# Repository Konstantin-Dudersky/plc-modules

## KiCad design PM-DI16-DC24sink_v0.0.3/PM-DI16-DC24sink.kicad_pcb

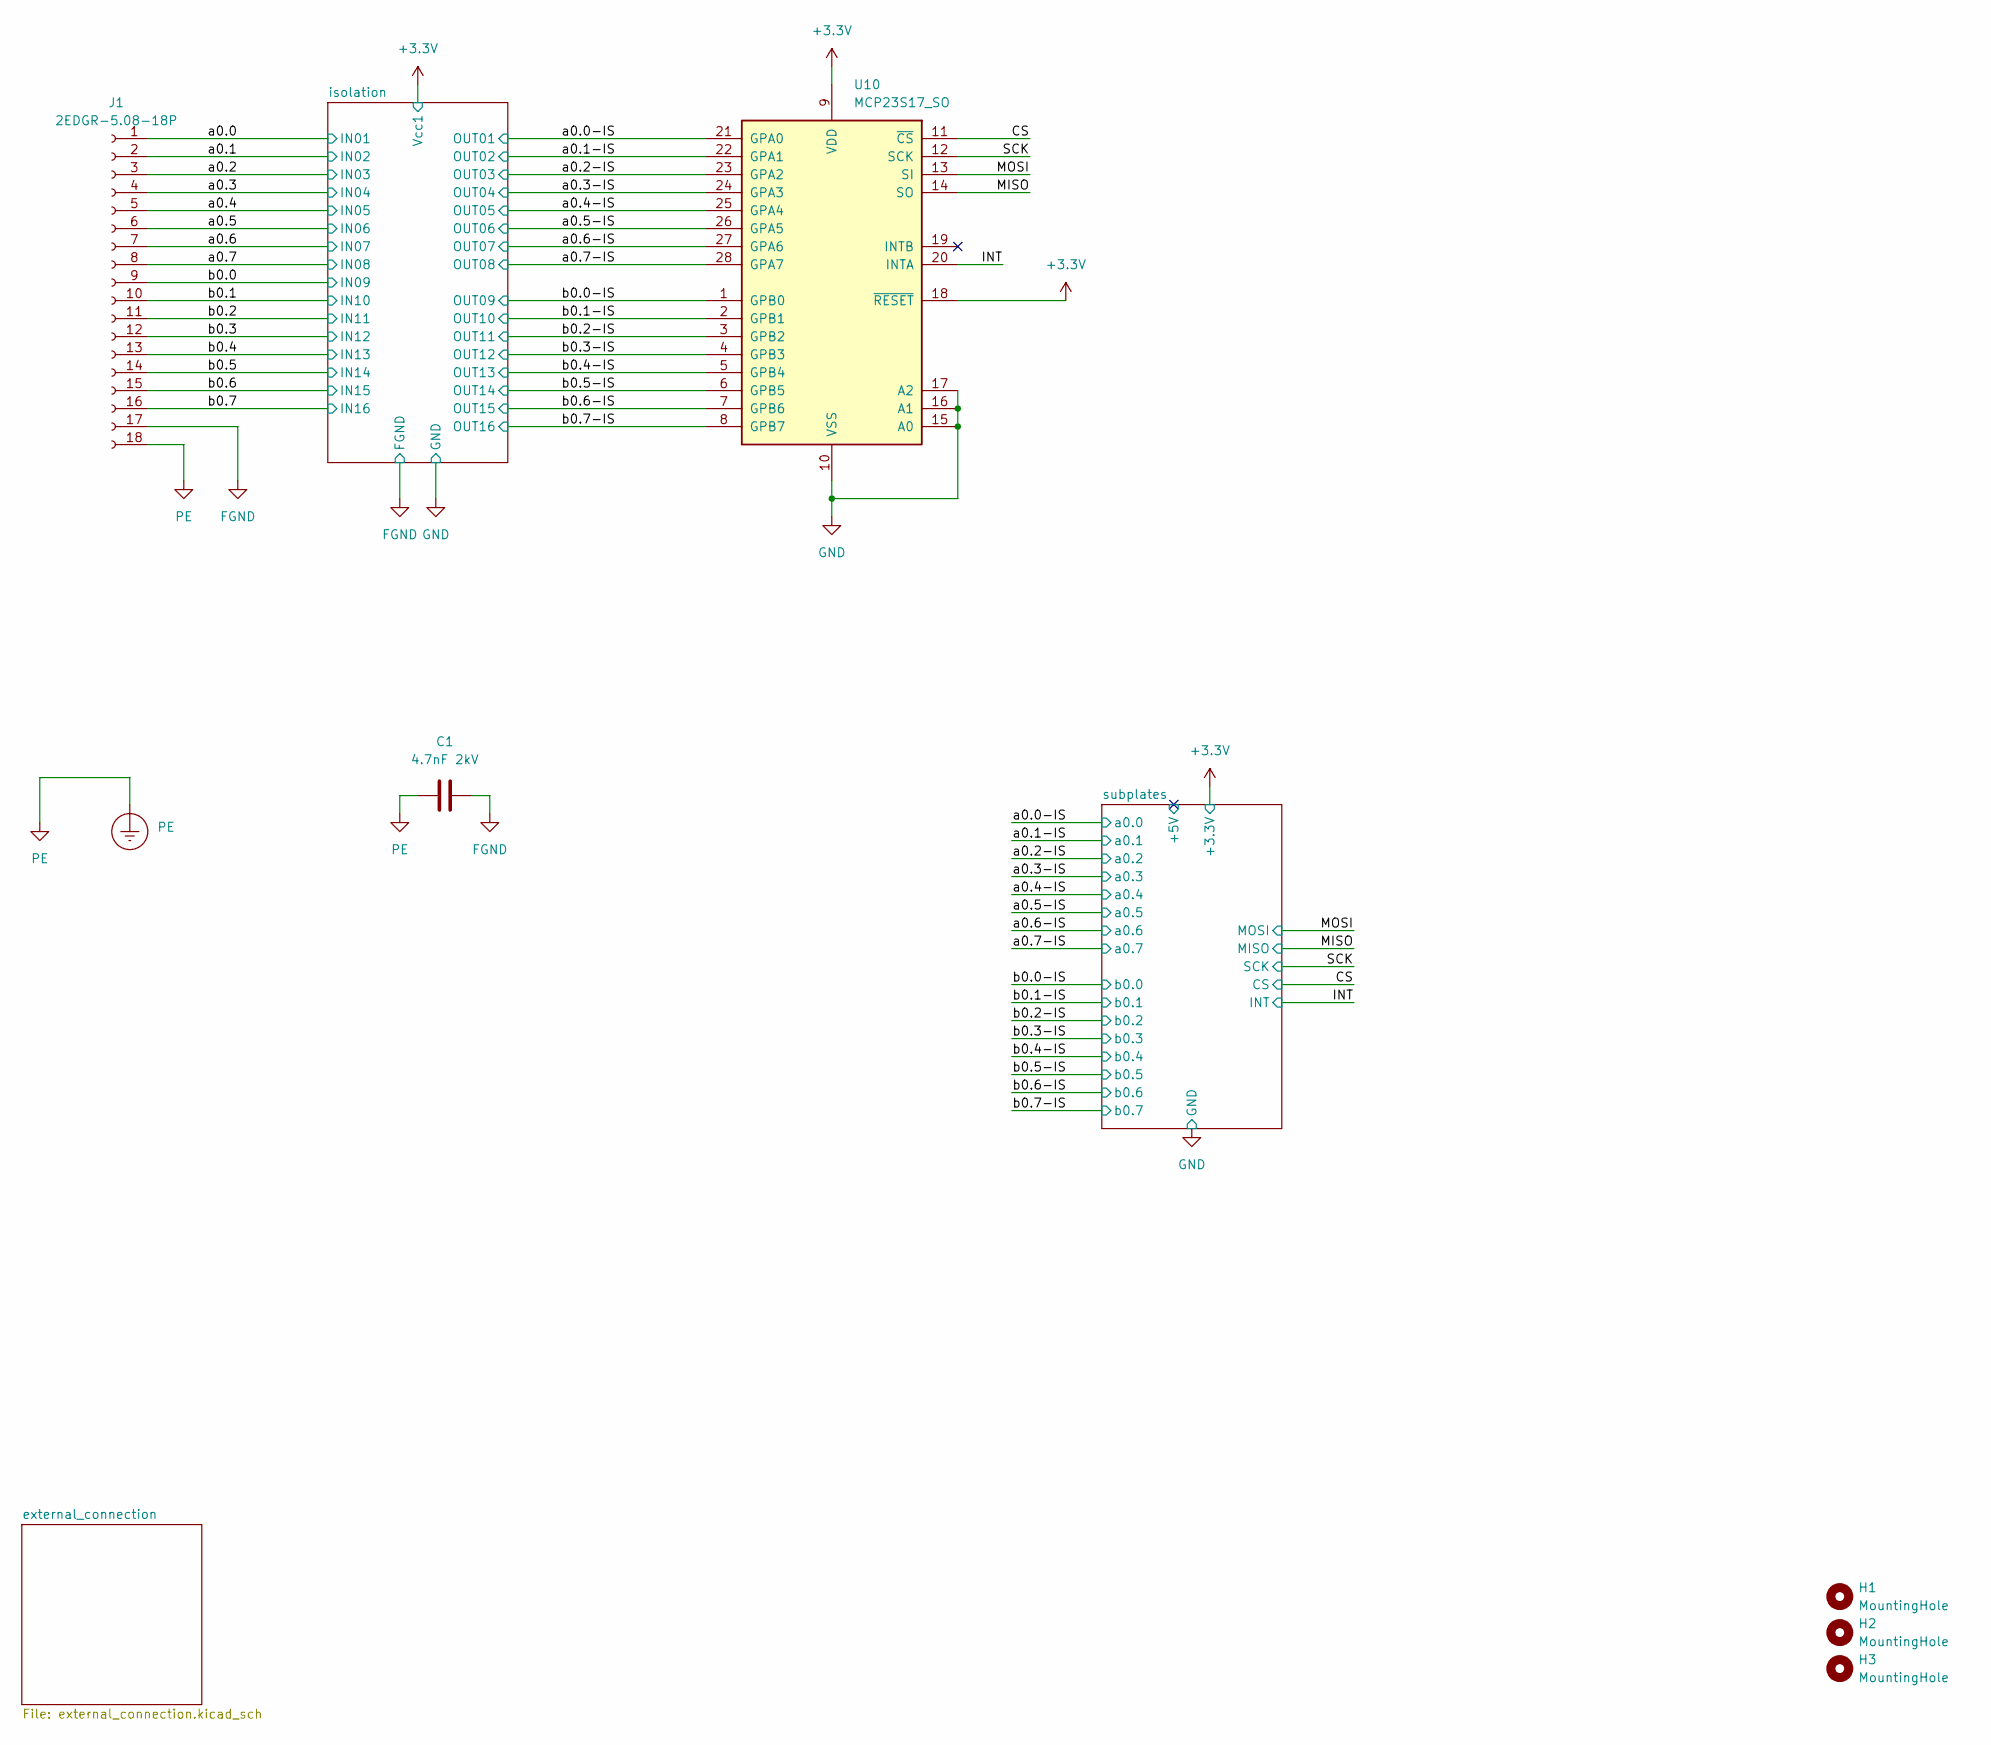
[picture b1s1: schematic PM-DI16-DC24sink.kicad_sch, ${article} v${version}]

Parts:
C1: 4.7nF 2kV; C_1812_4532Metric_Pad1.57x3.40mm_HandSolder; part_ipn C_4.7nF_2kV_1812
H1, H2, H3: MountingHole; MountingHole_3.2mm_M3
J1: 2EDGR-5.08-18P; Degson_2EDGR-5.08-18P; part_ipn 2EDGR-5.08-18P
PE1: PE
U10: MCP23S17_SO; SOIC-28W_7.5x17.9mm_P1.27mm; part_ipn MCP23S17-E/SO

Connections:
+3.3V: U10.9 (VDD), U10.18 (~RESET); also elsewhere on the board
/CS: U10.11 (~CS); also elsewhere on the board
/MISO: U10.14 (SO); also elsewhere on the board
/MOSI: U10.13 (SI); also elsewhere on the board
/SCK: U10.12 (SCK); also elsewhere on the board
/a0.0: J1.1; also elsewhere on the board
/a0.0-IS: U10.21 (GPA0); also elsewhere on the board
/a0.1: J1.2; also elsewhere on the board
/a0.1-IS: U10.22 (GPA1); also elsewhere on the board
/a0.2: J1.3; also elsewhere on the board
/a0.2-IS: U10.23 (GPA2); also elsewhere on the board
/a0.3: J1.4; also elsewhere on the board
/a0.3-IS: U10.24 (GPA3); also elsewhere on the board
/a0.4: J1.5; also elsewhere on the board
/a0.4-IS: U10.25 (GPA4); also elsewhere on the board
/a0.5: J1.6; also elsewhere on the board
/a0.5-IS: U10.26 (GPA5); also elsewhere on the board
/a0.6: J1.7; also elsewhere on the board
/a0.6-IS: U10.27 (GPA6); also elsewhere on the board
/a0.7: J1.8; also elsewhere on the board
/a0.7-IS: U10.28 (GPA7); also elsewhere on the board
/b0.0: J1.9; also elsewhere on the board
/b0.0-IS: U10.1 (GPB0); also elsewhere on the board
/b0.1: J1.10; also elsewhere on the board
/b0.1-IS: U10.2 (GPB1); also elsewhere on the board
/b0.2: J1.11; also elsewhere on the board
/b0.2-IS: U10.3 (GPB2); also elsewhere on the board
/b0.3: J1.12; also elsewhere on the board
/b0.3-IS: U10.4 (GPB3); also elsewhere on the board
/b0.4: J1.13; also elsewhere on the board
/b0.4-IS: U10.5 (GPB4); also elsewhere on the board
/b0.5: J1.14; also elsewhere on the board
/b0.5-IS: U10.6 (GPB5); also elsewhere on the board
/b0.6: J1.15; also elsewhere on the board
/b0.6-IS: U10.7 (GPB6); also elsewhere on the board
/b0.7: J1.16; also elsewhere on the board
/b0.7-IS: U10.8 (GPB7); also elsewhere on the board
FGND: C1.2, J1.17; also elsewhere on the board
GND: U10.10 (VSS), U10.15 (A0), U10.16 (A1), U10.17 (A2); also elsewhere on the board
PE: C1.1, J1.18, PE1.1

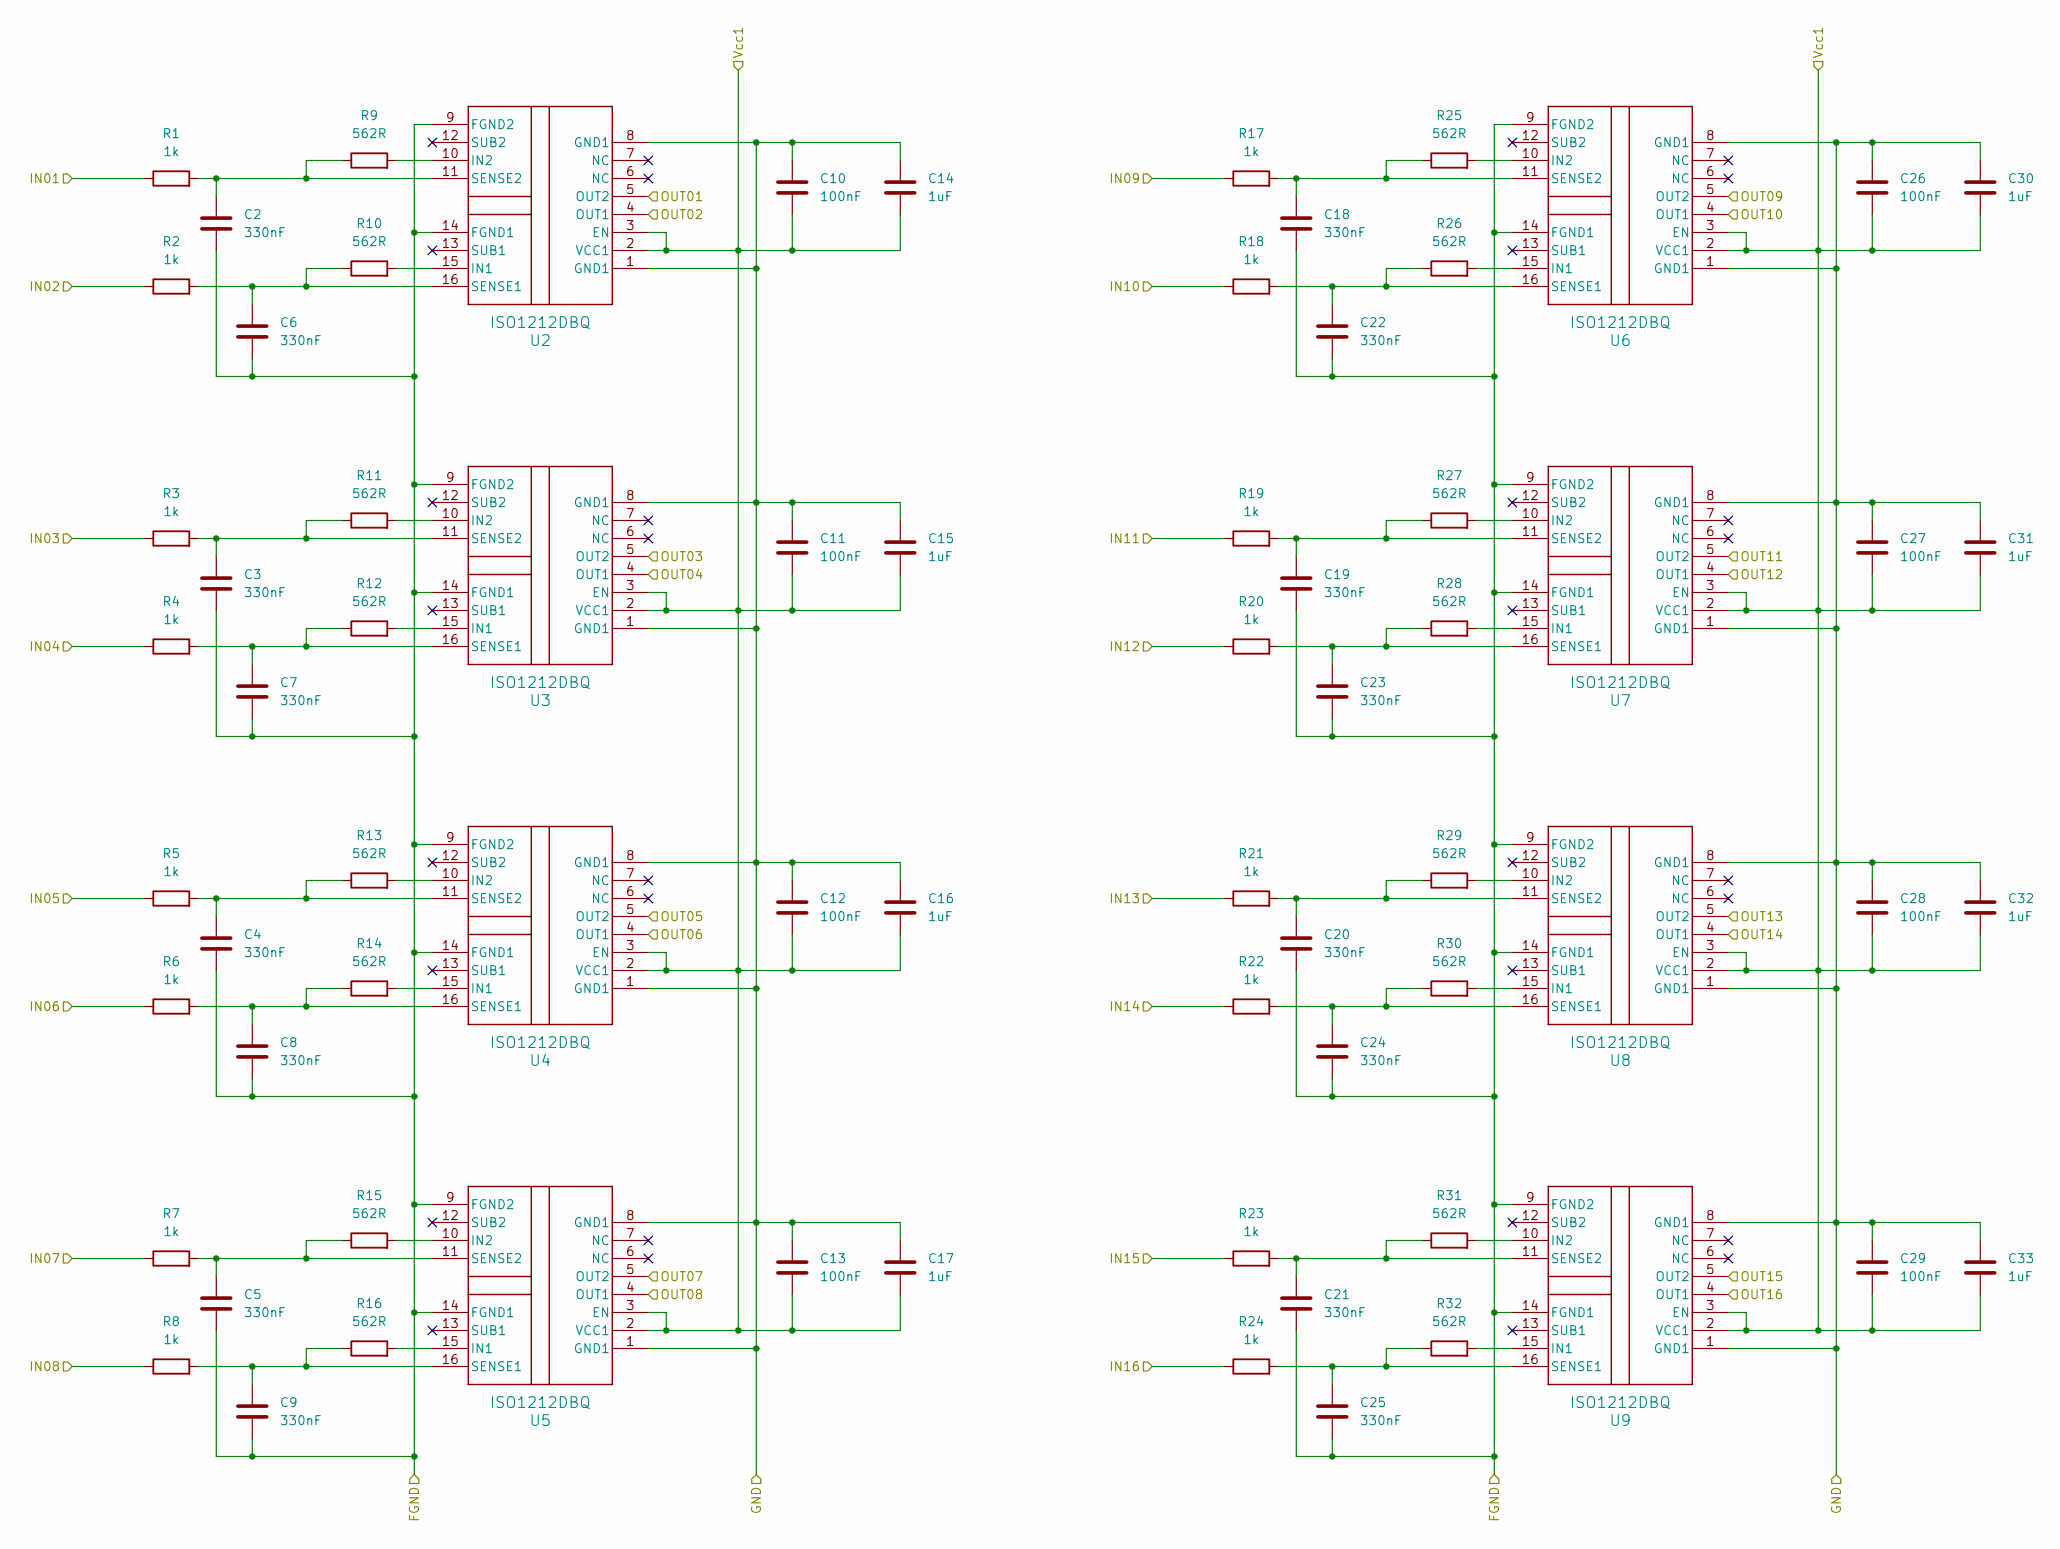
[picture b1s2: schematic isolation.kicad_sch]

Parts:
C2, C3, C4, C5, C6, C7, C8, C9, C18, C19, C20, C21, C22, C23, C24, C25: 330nF; C_1206_3216Metric_Pad1.33x1.80mm_HandSolder; part_ipn C_330nF_50V_1206
C10, C11, C12, C13, C26, C27, C28, C29: 100nF; C_1206_3216Metric_Pad1.33x1.80mm_HandSolder; part_ipn C_100nF_50V_1206
C14, C15, C16, C17, C30, C31, C32, C33: 1uF; C_1206_3216Metric_Pad1.33x1.80mm_HandSolder; part_ipn C_1uF_50V_1206
R1, R2, R3, R4, R5, R6, R7, R8, R17, R18, R19, R20, R21, R22, R23, R24: 1k; R_1206_3216Metric_Pad1.30x1.75mm_HandSolder; part_ipn R_1k_1206_1%
R9, R10, R11, R12, R13, R14, R15, R16, R25, R26, R27, R28, R29, R30, R31, R32: 562R; R_1206_3216Metric_Pad1.30x1.75mm_HandSolder; part_ipn R_562R_1206_1%
U2, U3, U4, U5, U6, U7, U8, U9: ISO1212DBQ; DBQ0016A_M; part_ipn ISO1212

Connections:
+3.3V: C10.2, C11.2, C12.2, C13.2, C14.2, C15.2, C16.2, C17.2, C26.2, C27.2, C28.2, C29.2, C30.2, C31.2, C32.2, C33.2, U2.2 (VCC1), U2.3 (EN), U3.2 (VCC1), U3.3 (EN), U4.2 (VCC1), U4.3 (EN), U5.2 (VCC1), U5.3 (EN), U6.2 (VCC1), U6.3 (EN), U7.2 (VCC1), U7.3 (EN), U8.2 (VCC1), U8.3 (EN), U9.2 (VCC1), U9.3 (EN); also elsewhere on the board
/a0.0: R1.1; also elsewhere on the board
/a0.0-IS: U2.5 (OUT2); also elsewhere on the board
/a0.1: R2.1; also elsewhere on the board
/a0.1-IS: U2.4 (OUT1); also elsewhere on the board
/a0.2: R3.1; also elsewhere on the board
/a0.2-IS: U3.5 (OUT2); also elsewhere on the board
/a0.3: R4.1; also elsewhere on the board
/a0.3-IS: U3.4 (OUT1); also elsewhere on the board
/a0.4: R5.1; also elsewhere on the board
/a0.4-IS: U4.5 (OUT2); also elsewhere on the board
/a0.5: R6.1; also elsewhere on the board
/a0.5-IS: U4.4 (OUT1); also elsewhere on the board
/a0.6: R7.1; also elsewhere on the board
/a0.6-IS: U5.5 (OUT2); also elsewhere on the board
/a0.7: R8.1; also elsewhere on the board
/a0.7-IS: U5.4 (OUT1); also elsewhere on the board
/b0.0: R17.1; also elsewhere on the board
/b0.0-IS: U6.5 (OUT2); also elsewhere on the board
/b0.1: R18.1; also elsewhere on the board
/b0.1-IS: U6.4 (OUT1); also elsewhere on the board
/b0.2: R19.1; also elsewhere on the board
/b0.2-IS: U7.5 (OUT2); also elsewhere on the board
/b0.3: R20.1; also elsewhere on the board
/b0.3-IS: U7.4 (OUT1); also elsewhere on the board
/b0.4: R21.1; also elsewhere on the board
/b0.4-IS: U8.5 (OUT2); also elsewhere on the board
/b0.5: R22.1; also elsewhere on the board
/b0.5-IS: U8.4 (OUT1); also elsewhere on the board
/b0.6: R23.1; also elsewhere on the board
/b0.6-IS: U9.5 (OUT2); also elsewhere on the board
/b0.7: R24.1; also elsewhere on the board
/b0.7-IS: U9.4 (OUT1); also elsewhere on the board
FGND: C2.2, C3.2, C4.2, C5.2, C6.2, C7.2, C8.2, C9.2, C18.2, C19.2, C20.2, C21.2, C22.2, C23.2, C24.2, C25.2, U2.9 (FGND2), U2.14 (FGND1), U3.9 (FGND2), U3.14 (FGND1), U4.9 (FGND2), U4.14 (FGND1), U5.9 (FGND2), U5.14 (FGND1), U6.9 (FGND2), U6.14 (FGND1), U7.9 (FGND2), U7.14 (FGND1), U8.9 (FGND2), U8.14 (FGND1), U9.9 (FGND2), U9.14 (FGND1); also elsewhere on the board
GND: C10.1, C11.1, C12.1, C13.1, C14.1, C15.1, C16.1, C17.1, C26.1, C27.1, C28.1, C29.1, C30.1, C31.1, C32.1, C33.1, U2.1 (GND1), U2.8 (GND1), U3.1 (GND1), U3.8 (GND1), U4.1 (GND1), U4.8 (GND1), U5.1 (GND1), U5.8 (GND1), U6.1 (GND1), U6.8 (GND1), U7.1 (GND1), U7.8 (GND1), U8.1 (GND1), U8.8 (GND1), U9.1 (GND1), U9.8 (GND1); also elsewhere on the board
unnamed: R10.2, U2.15 (IN1)
unnamed: R9.2, U2.10 (IN2)
unnamed: C6.1, R2.2, R10.1, U2.16 (SENSE1)
unnamed: C2.1, R1.2, R9.1, U2.11 (SENSE2)
unnamed: R12.2, U3.15 (IN1)
unnamed: R11.2, U3.10 (IN2)
unnamed: C7.1, R4.2, R12.1, U3.16 (SENSE1)
unnamed: C3.1, R3.2, R11.1, U3.11 (SENSE2)
unnamed: R14.2, U4.15 (IN1)
unnamed: R13.2, U4.10 (IN2)
unnamed: C8.1, R6.2, R14.1, U4.16 (SENSE1)
unnamed: C4.1, R5.2, R13.1, U4.11 (SENSE2)
unnamed: R16.2, U5.15 (IN1)
unnamed: R15.2, U5.10 (IN2)
unnamed: C9.1, R8.2, R16.1, U5.16 (SENSE1)
unnamed: C5.1, R7.2, R15.1, U5.11 (SENSE2)
unnamed: R26.2, U6.15 (IN1)
unnamed: R25.2, U6.10 (IN2)
unnamed: C22.1, R18.2, R26.1, U6.16 (SENSE1)
unnamed: C18.1, R17.2, R25.1, U6.11 (SENSE2)
unnamed: R28.2, U7.15 (IN1)
unnamed: R27.2, U7.10 (IN2)
unnamed: C23.1, R20.2, R28.1, U7.16 (SENSE1)
unnamed: C19.1, R19.2, R27.1, U7.11 (SENSE2)
unnamed: R30.2, U8.15 (IN1)
unnamed: R29.2, U8.10 (IN2)
unnamed: C24.1, R22.2, R30.1, U8.16 (SENSE1)
unnamed: C20.1, R21.2, R29.1, U8.11 (SENSE2)
unnamed: R32.2, U9.15 (IN1)
unnamed: R31.2, U9.10 (IN2)
unnamed: C25.1, R24.2, R32.1, U9.16 (SENSE1)
unnamed: C21.1, R23.2, R31.1, U9.11 (SENSE2)

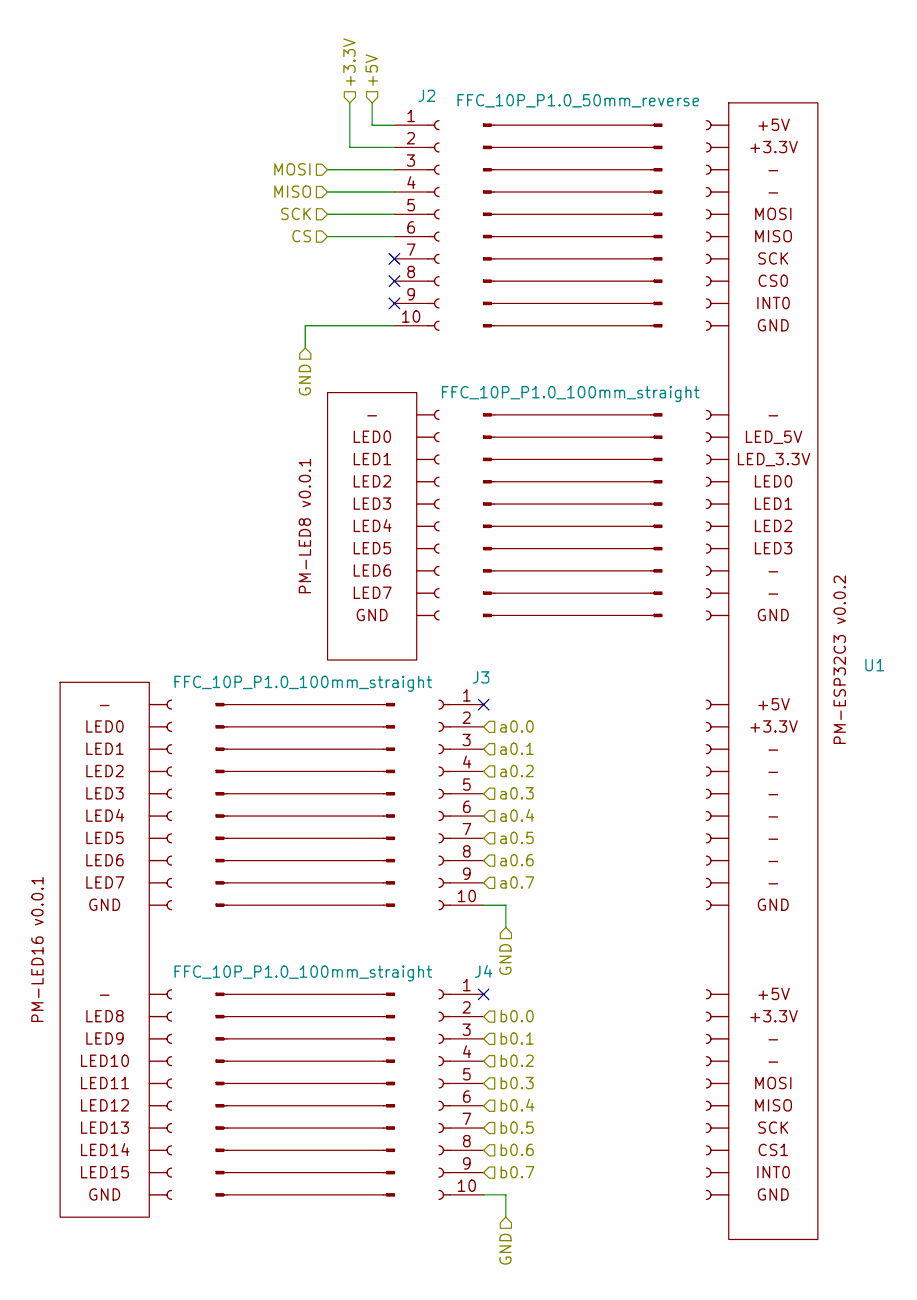
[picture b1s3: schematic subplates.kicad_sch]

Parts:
J2, J3, J4: AFA07-S10FCC-00; CONN10_AFA07-S10_JUS
J5: FFC_10P_P1.0_50mm_reverse; part_ipn FFC_10P_P1.0_50mm_reverse
J6, J7, J8: FFC_10P_P1.0_100mm_straight; part_ipn FFC_10P_P1.0_100mm_straight
U1: PM-ESP32C3_v0.0.2
U11: PM-LED8_v0.0.1; PM-LED_v0.0.1
U12: PM-LED16_v0.0.1; PM-LED_v0.0.1

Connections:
+3.3V: J2.2; also elsewhere on the board
/CS: J2.6; also elsewhere on the board
/MISO: J2.4; also elsewhere on the board
/MOSI: J2.3; also elsewhere on the board
/SCK: J2.5; also elsewhere on the board
/a0.0-IS: J3.2; also elsewhere on the board
/a0.1-IS: J3.3; also elsewhere on the board
/a0.2-IS: J3.4; also elsewhere on the board
/a0.3-IS: J3.5; also elsewhere on the board
/a0.4-IS: J3.6; also elsewhere on the board
/a0.5-IS: J3.7; also elsewhere on the board
/a0.6-IS: J3.8; also elsewhere on the board
/a0.7-IS: J3.9; also elsewhere on the board
/b0.0-IS: J4.2; also elsewhere on the board
/b0.1-IS: J4.3; also elsewhere on the board
/b0.2-IS: J4.4; also elsewhere on the board
/b0.3-IS: J4.5; also elsewhere on the board
/b0.4-IS: J4.6; also elsewhere on the board
/b0.5-IS: J4.7; also elsewhere on the board
/b0.6-IS: J4.8; also elsewhere on the board
/b0.7-IS: J4.9; also elsewhere on the board
/subplates/+5V: J2.1
GND: J2.10, J3.10, J4.10; also elsewhere on the board

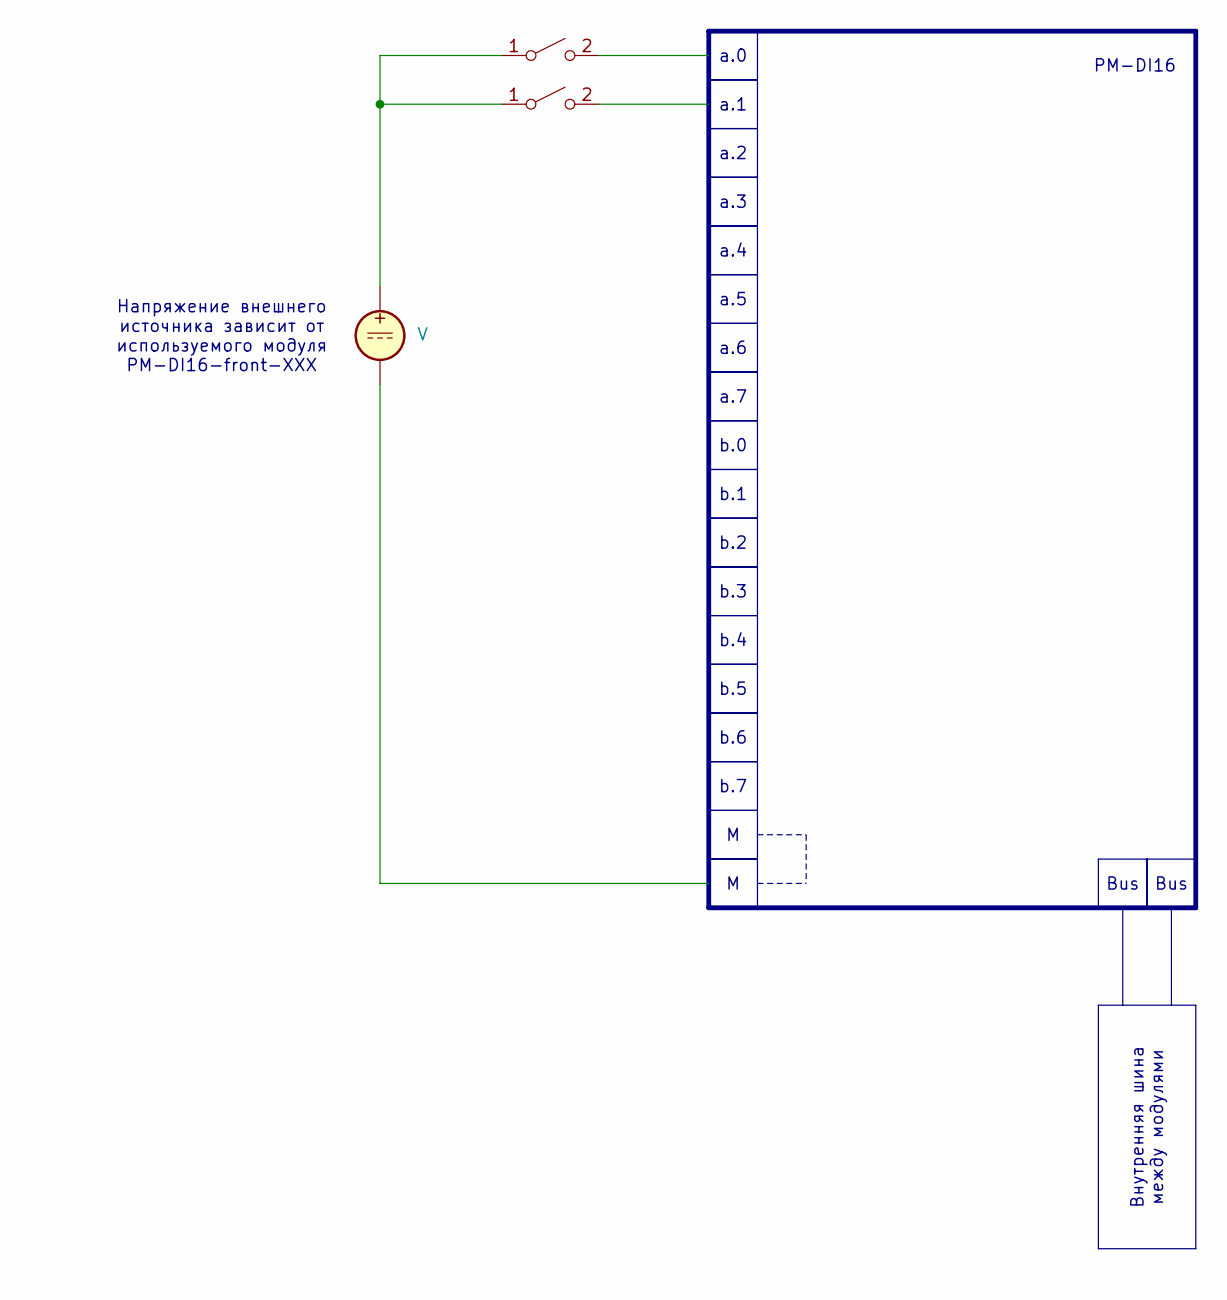
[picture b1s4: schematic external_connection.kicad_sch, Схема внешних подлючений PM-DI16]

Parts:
SW1, SW2: SW_SPST
V: 1

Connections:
unnamed: SW1.1 (A), SW2.1 (A), V.1

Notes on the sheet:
Напряжение внешнего источника зависит от используемого модуля PM-DI16-front-XXX
b.2
Bus
a.3
a.6
b.5
b.1
a.0
b.0
Внутренняя шина между модулями
a.5
b.7
a.4
b.3
b.4
a.7
b.6
a.1
a.2
PM-DI16

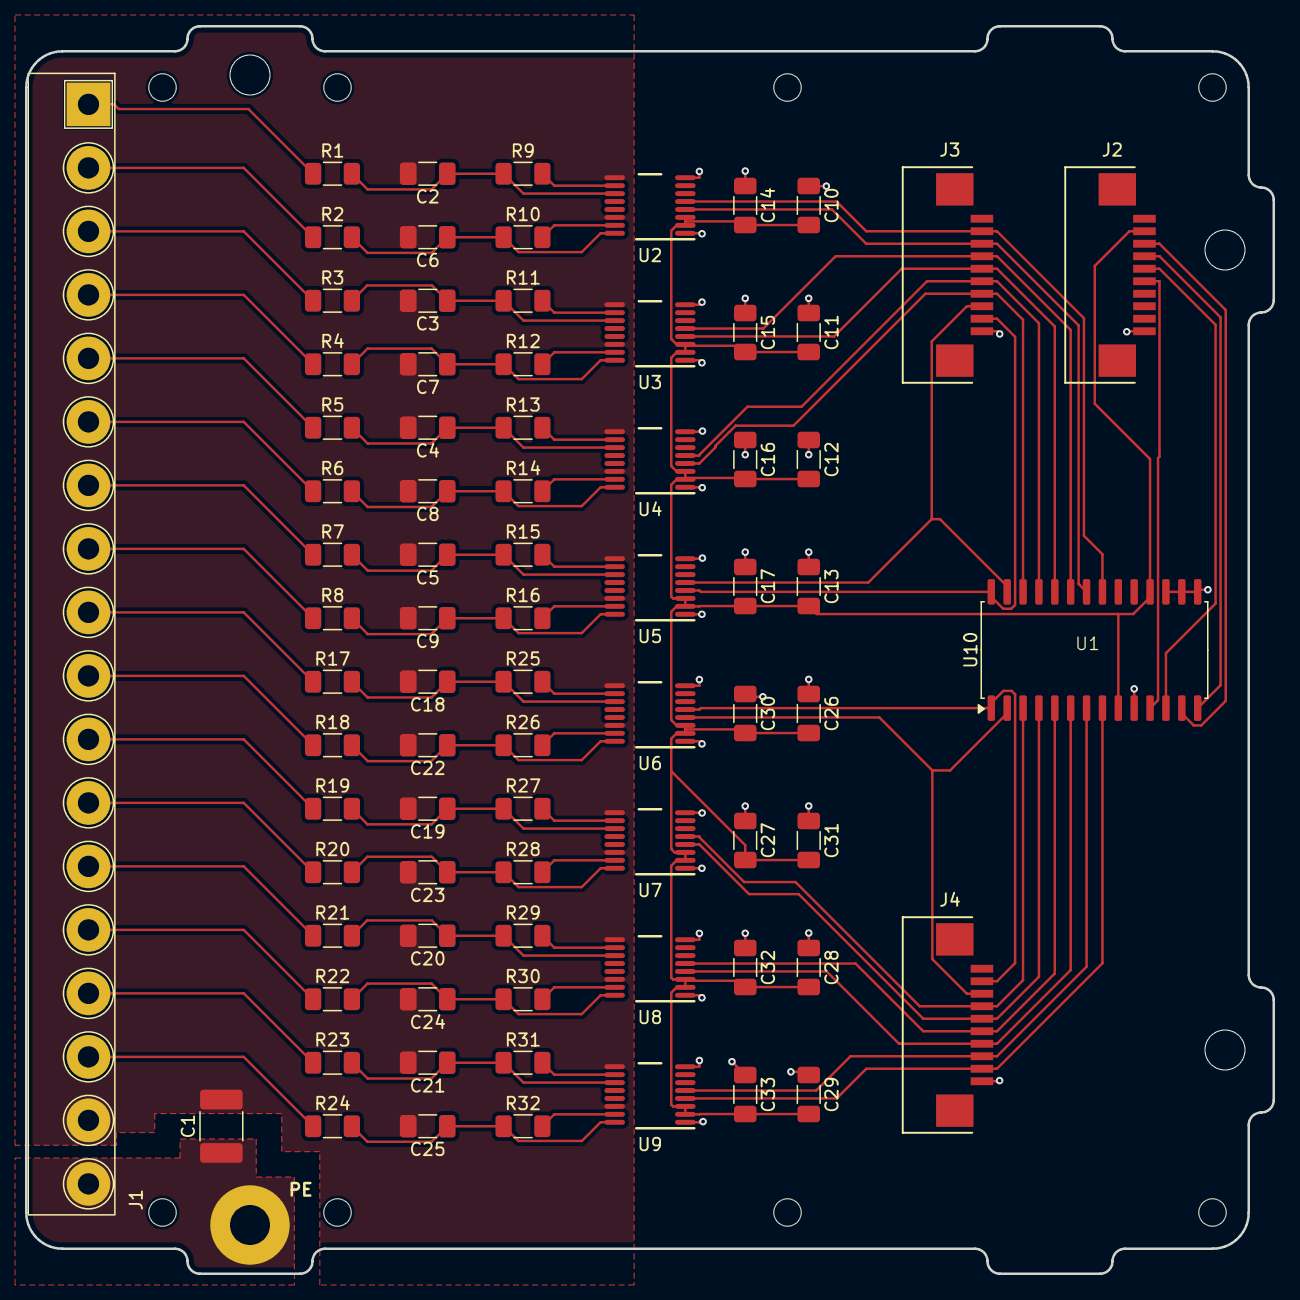
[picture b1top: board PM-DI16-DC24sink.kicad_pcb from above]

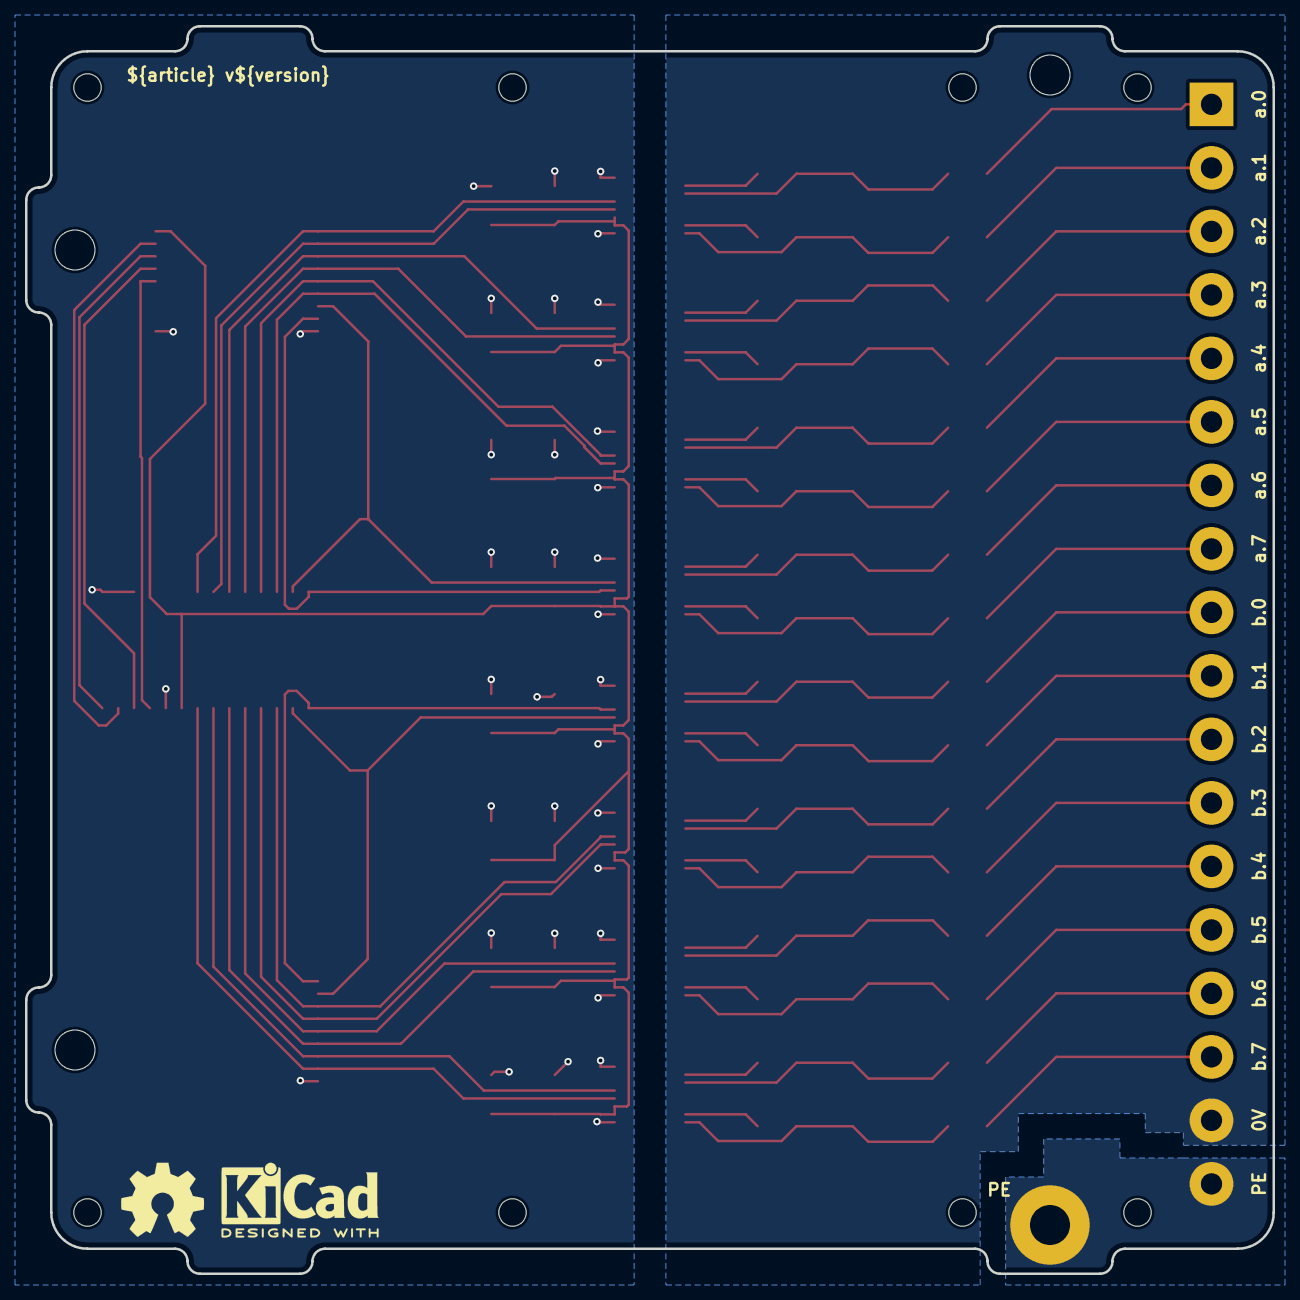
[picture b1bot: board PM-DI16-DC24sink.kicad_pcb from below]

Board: 2 copper layers, 99.8 x 99.8 mm, 86 parts (2 on the bottom side), 72 nets.

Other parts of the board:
kicad_logo: KiCad-Logo2_5mm_SilkScreen
oshw_logo: OSHW-Symbol_6.7x6mm_SilkScreen
